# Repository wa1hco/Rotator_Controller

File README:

Rotator_Controller derives from the K3NG rotator controller code.

The changes include
--- Developed for Teensy 3 and 4 series microcontroller
--- Version for HCO_board with relays and 7 segment
--- BigFont for 4x20 lcd to make it more like the GreenHeron controller
--- Lots of changes to better suit my programming style
--- Scratchy pot filter for rotors with grounded wiper

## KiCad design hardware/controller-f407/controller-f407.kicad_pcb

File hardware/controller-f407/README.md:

# F407 controller schematic

This is the new controller, started from the outside in. The rotor interface and the AC motor drive are on `rotor_drive`. The Drive MCU and the analog front end are the next two sheets.

The directory is `hardware/controller-f407/` because ADR 0014 names the STM32F407, and the tree sits beside the imported V4 project at `hardware/controller/` without mixing files. Leave `hardware/controller/` untouched. It is the reference for the V4 TVS, snubber, and connector practice.

| File | What it is |
| --- | --- |
| `controller-f407.kicad_sch` | Root sheet. `rotor_drive`, `drive_mcu`, and `analog_input` hang off it. `+5V` and `AC_FUSED` stay no-connects until the power sheet exists. |
| `rotor_drive.kicad_sch` | Azimuth rotor connector, motor caps, triac drive, ARM relay, 26 VAC tap. |
| `drive_mcu.kicad_sch` | Drive MCU, STM32G431RBT6. Power, SWD, and the UART to the Station. |
| `analog_input.kicad_sch` | Pot front end, the VIN_RECT warning, and the ADC reference filter. |
| `rotor-drive.pdf` | Plot of both sheets, for review away from KiCad. |
| `DESIGN-NOTES.md` | What each block does, the calculations, the bill of materials, and the open questions. |
| `symbols/controller-f407.kicad_sym` | Unused TPS3823-33 symbol (the supervisor is not on the rotor sheet) and the no-pad Powerpole gland marker. |
| `footprints/controller-f407.pretty/` | The two motor-cap footprints copied from the Hammond outline, and the gland marker. |

KiCad 9. Nets leave `rotor_drive` on hierarchical labels (`AZ_CW_EN`, `AZ_CCW_EN`, `AZ_BRAKE_EN`, `ARM_EN`, `ZC_SENSE`, and the rest listed in the design notes). The pin assignment is in [the Drive note](../../docs/design/drive-controller.md). Through-hole parts are bought from Mouser. SMT parts that have a checked LCSC number say so on the symbol; the rest are TBD.

Elevation is a later copy of this sheet (ADR 0008), not a second channel here.

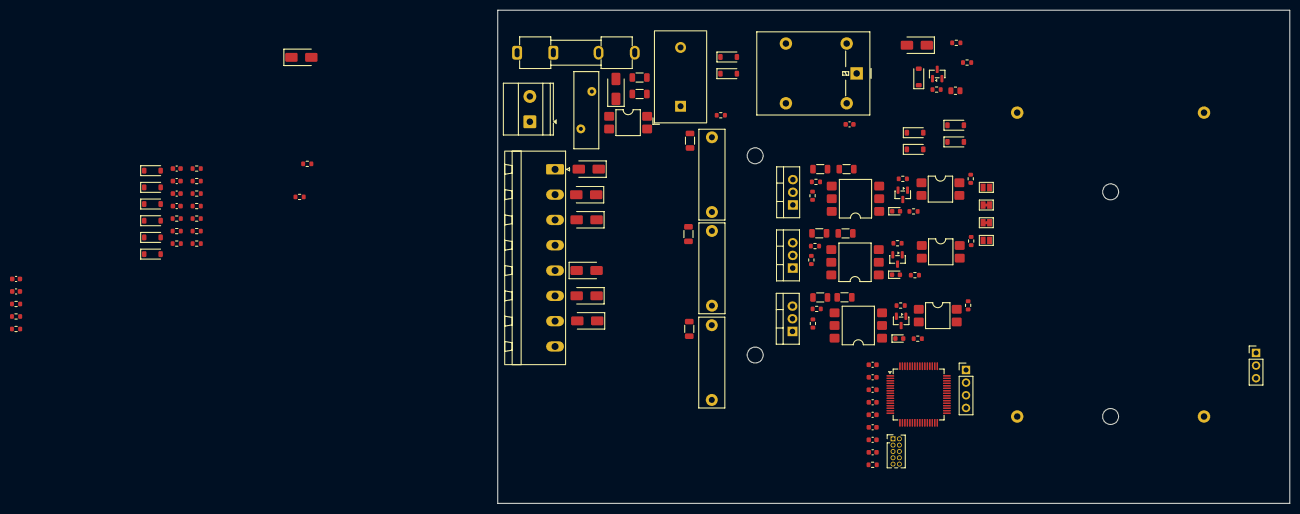
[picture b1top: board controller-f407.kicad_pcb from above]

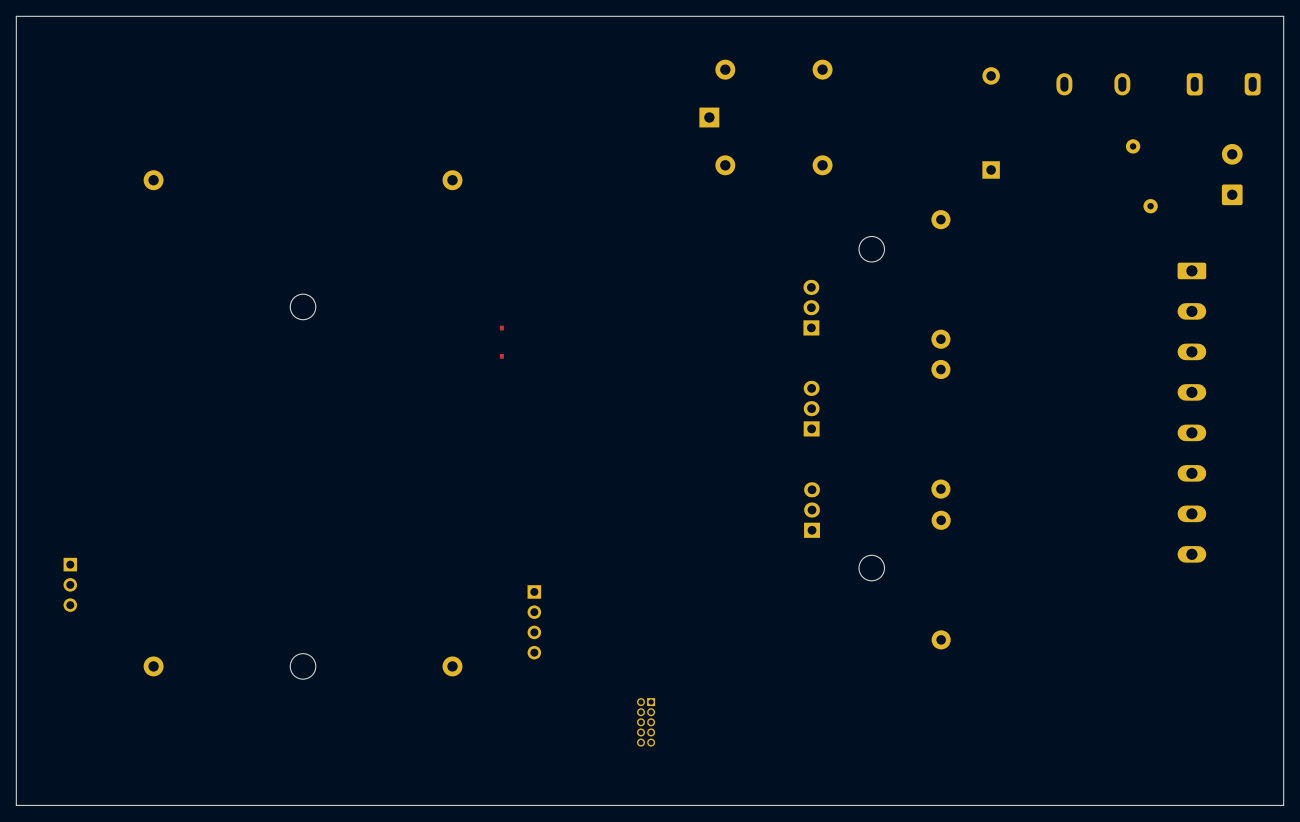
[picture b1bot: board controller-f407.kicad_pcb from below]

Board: 2 copper layers, 159.0 x 99.0 mm, 122 parts (2 on the bottom side), 72 nets, no tracks yet.

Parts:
C1, C2, C3: 100nF; C_0603_1608Metric
C4, C5, C8: 100nF; C_Rect_L18.0mm_W5.0mm_P15.00mm_FKS3_FKP3
C6: 100uF; C_Rect_KEMET_R60_P37.5_L41.5_W20_H40_Flat
C7: 33uF; C_Rect_TDK_B32526T_P37.5_L41.5_W24_H15_Upright
C9, C11, C12, C13, C14, C16, C17, C18, C19, C20: 100n; C_0603_1608Metric
C10: 1u; C_0603_1608Metric
C15: 4.7u; C_0603_1608Metric
D1, D2, D14, D15, D16, D17, D18, D20, D21, D23, D24, D25: BAT54; D_SOD-123
D3: S1M; D_SMA
D4, D8, D9, D10, D11, D12, D19, D22: SMAJ90CA; D_SMA
D5: 1N4148W; D_SOD-123
D6, D7, D13: RED; LED_0603_1608Metric
F1: T6.3A; Fuseholder_Clip-5x20mm_Keystone_3512_Inline_P23.62x7.27mm_D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
HS1: AL_BAR_10x50 + 2x NPTH 3.2; AL_BAR_10x50
J1: AC_PIGTAIL; TerminalBlock_Phoenix_MKDS-1,5-2-5.08_1x02_P5.08mm_Horizont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
J2: CDE_1to8; PhoenixContact_MSTBA_2,5_8-G-5,08_1x08_P5.08mm_Horizontal
J3: SWD; PinHeader_2x05_P1.27mm_Vertical
J4: UART; PinHeader_1x04_P2.54mm_Vertical
J5: EL_POT; PinHeader_1x03_P2.54mm_Vertical
K1: G5LE-1A4-DC5; Relay_SPDT_Omron-G5LE-1
MK1: PWR_GLAND; Panel_Gland_M16
Q1: AO3400A; SOT-23
Q2, Q4, Q6: BTA16-600SWRG; TO-220-3_Vertical
Q3, Q5, Q7: 2N7002; SOT-23
R1, R4, R5, R15, R22, R29, R33, R36, R39, R42: 10k; R_0603_1608Metric
R2, R11, R18, R25, R32, R35, R38, R41, R44: 1k; R_0603_1608Metric
R2G1, R3G1, R4G1, R8: 100k; R_0603_1608Metric
R3: 100; R_0805_2012Metric
R6, R7, R12, R14, R19, R21, R26, R28: 7.5k; R_1206_3216Metric
R9, R16, R23: 100; R_0603_1608Metric
R10, R17, R24: 180; R_0603_1608Metric
R13, R20, R27: 68; R_1206_3216Metric
R30: 10; R_0603_1608Metric
R31, R34, R37, R40: 330; R_0603_1608Metric
R43: 39k; R_0603_1608Metric
RV1: 35VAC; RV_Disc_D15.5mm_W5mm_P7.5mm
SJ1: YAE_CAP_A; SolderJumper-2_P1.3mm_Open_Pad1.0x1.5mm
SJ2: CDE_CAP_A; SolderJumper-2_P1.3mm_Bridged_Pad1.0x1.5mm
SJ3: CDE_CAP_B; SolderJumper-2_P1.3mm_Bridged_Pad1.0x1.5mm
SJ4: YAE_CAP_B; SolderJumper-2_P1.3mm_Open_Pad1.0x1.5mm
TR1: ZMCT103C; Transformer_Zeming_ZMCT103C
U1, U3, U5, U7: LTV-814S-TA1; SMDIP-4_W7.62mm
U2, U4, U6: MOC3023SM; SMDIP-6_W9.53mm
U8: STM32G431RBTx; LQFP-64_10x10mm_P0.5mm

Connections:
/+3V3: C3.1, C11.1, C12.1, C13.1, C14.1, C15.1, D1.1 (K), D14.1 (K), D16.1 (K), D18.1 (K), D21.1 (K), D24.1 (K), J3.1, J4.2, R1.1, R5.1, R15.1, R22.1, R29.1, R30.2, R31.1, R34.1, R37.1, R40.1, U8.1 (VBAT), U8.16 (VDD), U8.32 (VDD), U8.48 (VDD), U8.64 (VDD)
/ARM_EN: Q1.1 (G), R8.1, U8.55 (PD2)
/AZ_A_ADC: C17.1, R33.2, U8.8 (PC0)
/AZ_BRAKE_EN: Q3.1 (G), R4G1.1, U8.54 (PC12)
/AZ_BRAKE_SNS: R15.2, U3.4, U8.4 (PC15)
/AZ_B_ADC: C18.1, R36.2, U8.9 (PC1)
/AZ_CCW_EN: Q7.1 (G), R3G1.1, U8.39 (PC7)
/AZ_CCW_SNS: R29.2, U7.4, U8.3 (PC14)
/AZ_CW_EN: Q5.1 (G), R2G1.1, U8.38 (PC6)
/AZ_CW_SNS: R22.2, U5.4, U8.2 (PC13)
/AZ_POT_3: D9.2 (A2), J2.3, R31.2, R32.1
/AZ_POT_7: D12.2 (A2), J2.7, R34.2, R35.1
/EL_A_ADC: C19.1, R39.2, U8.10 (PC2)
/EL_B_ADC: C20.1, R42.2, U8.11 (PC3)
/I_ADC: D1.2 (A), D2.1 (K), R2.2, U8.12 (PA0)
/VIN_RECT: D3.1 (K), R43.1
/VIN_WARN: D24.2 (A), D25.1 (K), R43.2, R44.1, U8.13 (PA1)
/ZC_SENSE: R5.2, U1.4, U8.58 (PB5)
/analog_input/EL_POT_A: D19.1 (K), J5.2, R37.2, R38.1
/analog_input/EL_POT_B: D22.1 (K), J5.3, R40.2, R41.1
/rotor_drive/+5V: C2.1, D5.1 (K), K1.5, R10.1, R17.1, R24.1
/rotor_drive/AC_BUS: K1.3, Q2.2 (A2), Q4.2 (A2), Q6.2 (A2), R12.1, R13.1, R19.1, R20.1, R26.1, R27.1
/rotor_drive/AC_FUSED: D3.2 (A), D4.2 (A2), F1.2, K1.1, R7.1, RV1.1
/rotor_drive/BRK_OUT: C4.2, D8.2 (A2), J2.2, Q2.1 (A1), R11.2, U2.4, U3.2
/rotor_drive/CCW_OUT: C8.2, D11.2 (A2), J2.6, Q6.1 (A1), R25.2, SJ4.2 (B), U6.4, U7.2
/rotor_drive/CW_OUT: C5.2, D10.2 (A2), J2.5, Q4.1 (A1), R18.2, SJ1.2 (B), U4.4, U5.2
/rotor_drive/I_BIAS: C1.1, R1.2, R3.2, R4.1, TR1.1
/rotor_drive/I_CT: R2.1, R3.1, TR1.2
/rotor_drive/TB4: J2.4, SJ2.2 (B)
/rotor_drive/TB8: J2.8, SJ3.2 (B)
GNDPWR: C1.2, C2.2, C3.2, C9.2, C10.2, C11.2, C12.2, C13.2, C14.2, C15.2, C16.2, C17.2, C18.2, C19.2, C20.2, D2.2 (A), D4.1 (A1), D8.1 (A1), D9.1 (A1), D10.1 (A1), D11.1 (A1), D12.1 (A1), D15.2 (A), D17.2 (A), D19.2 (A), D20.2 (A), D22.2 (A), D23.2 (A), D25.2 (A), J1.2, J2.1, J3.3, J3.5, J3.9, J4.1, J5.1, Q1.2 (S), Q3.2 (S), Q5.2 (S), Q7.2 (S), R2G1.2, R3G1.2, R4.2, R4G1.2, R8.2, R44.2, RV1.2, U1.2, U1.3, U3.3, U5.3, U7.3, U8.15 (VSS), U8.27 (VSSA), U8.31 (VSS), U8.47 (VSS), U8.63 (VSS)
unnamed: C4.1, R13.2
unnamed: C5.1, R20.2
unnamed: C8.1, R27.2
unnamed: D5.2 (A), K1.2, Q1.3 (D)
unnamed: D6.2 (A), R10.2
unnamed: D6.1 (K), U2.1
unnamed: D7.2 (A), R17.2
unnamed: D7.1 (K), U4.1
unnamed: D13.2 (A), R24.2
unnamed: D13.1 (K), U6.1
unnamed: D14.2 (A), D15.1 (K), R32.2, R33.1
unnamed: D16.2 (A), D17.1 (K), R35.2, R36.1
unnamed: D18.2 (A), D20.1 (K), R38.2, R39.1
unnamed: D21.2 (A), D23.1 (K), R41.2, R42.1
unnamed: F1.1, J1.1
unnamed: Q2.3 (G), R9.2, R11.1
unnamed: Q3.3 (D), U2.2
unnamed: Q4.3 (G), R16.2, R18.1
unnamed: Q5.3 (D), U4.2
unnamed: Q6.3 (G), R23.2, R25.1
unnamed: Q7.3 (D), U6.2
unnamed: R6.1, R7.2
unnamed: R6.2, U1.1
unnamed: R9.1, U2.6
unnamed: R12.2, R14.1
unnamed: R14.2, U3.1
unnamed: R16.1, U4.6
unnamed: R19.2, R21.1
unnamed: R21.2, U5.1
unnamed: R23.1, U6.6
unnamed: R26.2, R28.1
unnamed: R28.2, U7.1
unnamed: C6.1, C7.1, SJ1.1 (A), SJ2.1 (A)
unnamed: C6.2, C7.2, SJ3.1 (A), SJ4.1 (A)
unnamed: J3.2, U8.49 (PA13)
unnamed: J3.4, U8.50 (PA14)
unnamed: J3.6, U8.56 (PB3)
unnamed: J4.3, U8.30 (PB10)
unnamed: J4.4, U8.33 (PB11)
unnamed: C16.1, J3.10, U8.7 (PG10)
unnamed: C9.1, C10.1, R30.1, U8.28 (VREF+), U8.29 (VDDA)

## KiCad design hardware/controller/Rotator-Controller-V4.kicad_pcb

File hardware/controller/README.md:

# V4 controller board

KiCad 9 project for the shack-side antenna rotator controller. The files
in this directory are the imported CPC1966 design: STM32F405RGT6 in
LQFP-64, ADuM4160 isolated USB, and three CPC1966 AC solid-state relays
(CW, CCW, brake).

That MCU is not the build target. The accepted part is an STM32F407VGT6
(LQFP-100, LCSC C12345) with a LAN8720A RMII PHY, and Ethernet is
standard. See `docs/decisions/0014-stm32f407-lan8720.md` and
`docs/design/mcu-ethernet-lcsc.md`. The schematic and PCB are
intentionally not edited for that change. The MCU area was barely
routed, so the next layout pass replaces the 64-pin footprint.

Newer edits that exist only on the owner's laptop are **not** in this
import. Those are the discrete-triac swap (MOC3023M + BTA16-600SW and
snubbers) and the annotated design notes. They will be added later.
Until then, `docs/design/v4-discrete-triac-change.md` is the change plan,
and the schematic still shows CPC1966 parts.

## Assembly and part fields

JLCPCB assembles every SMT part, and those parts come from the LCSC
catalog. The owner hand-solders every through-hole part, and those parts
are bought from Mouser. The record is
`docs/decisions/0013-assembly-sourcing.md`.

When symbols are updated (not done in the imported project):

- An SMT part gets an `LCSC` field whose value is the LCSC C-number
  (for example `C12345` on the STM32F407VGT6).
- A through-hole part gets a `Mouser` field with the Mouser order number.
The RJ45 candidate is the Pulse J0011D01BNL; that order number is not
confirmed yet, so the field waits until it is.

## Programming and debug (not in the schematic yet)

The next layout adds these. Details and the reasons are in
`docs/decisions/0015-configuration-and-ui.md` and the programming
addendum of `docs/design/hardware-requirements.md`. Do not put them on
the front plate.

| Function | Part | Source field |
|---|---|---|
| BOOT0 tactile, pull-down to ground, button to 3.3 V | SMT tactile. C-number TBD | `LCSC` when known |
| RESET tactile, to NRST | SMT tactile. C-number TBD | `LCSC` when known |
| PB2 (BOOT1) pull-down | SMT resistor. C-number TBD | `LCSC` when known |
| MCU HSE | 8 MHz crystal and load caps. C-numbers TBD. Not the PHY's 25 MHz C9006 | `LCSC` when known |
| USB-C CC1 and CC2 | 5.1 kΩ each to ground. C-number TBD | `LCSC` when known |
| Debug | Tag-Connect TC2050-IDC-NL pads (SWDIO, SWCLK, SWO, NRST). No part | none |
| Boot LED | SMT LED and resistor. C-numbers TBD | `LCSC` when known |

USB-C D+ does not get its own 1.5 kΩ. The ADuM4160's PIN pin is tied to
VDD2 so the isolator's upstream pull-up is present for ROM DFU and for
the application. SPU and SPD are tied high (full speed). The drawing
still straps them low.

## Source

Imported from [wa1hco/Rotator-Controller-V2](https://github.com/wa1hco/Rotator-Controller-V2),
branch `Rotator_Controller_V4`, commit
`27affb32f34605df6d436127cd1c47bb30fbcdb9`
("Removed some deleted files", 2025-10-09).

History was kept with `git filter-repo`: only the KiCad project and the
project-local libraries this board references were retained, then moved
under `hardware/controller/`. Commit hashes in this repository differ
from the source repo because the history was rewritten. The last source
commit that changed the schematic is
`b3b3aa526a4143c245adb577c08cf79c1521e6af`. Blob hashes of every imported
file match the source tip above. The source tip commit itself only
deleted files that were not imported, so it does not appear in this history.

That source tree was published under CC0-1.0. The same author licenses
the hardware in **this** repository under CERN-OHL-S-2.0
(`hardware/LICENSE`).

## What was kept

| Path | Why |
|---|---|
| `Rotator-Controller-V4.kicad_{pro,sch,pcb}` | The board |
| `RotatorController.kicad_sym`, `RotatorController.pretty/` | CPC1966 symbol and footprint, both used |
| `LightPipe.kicad_sym`, `Lightpipe.pretty/` | LP4-EP light pipe, used |
| `NKK_BB15AH.pretty/` | Front-panel switch footprint, used |
| `sym-lib-table`, `fp-lib-table` | Project library tables |
| `.gitignore` | KiCad backup and cache rules from the source project |

Library nicknames and `${KIPRJMOD}` URIs are unchanged for the libraries
that remain, so opening the project from this directory does not depend
on a global KiCad library path. After the move, table entries for
libraries that were **not** imported (Teensy, Button, Pushbutton) were
removed. Leaving them would make KiCad look for missing directories.

Symbols are also embedded in the schematic, and footprints are embedded
in the PCB, which is how KiCad 6+ projects open when a library is absent.
The project-local libraries are still here so "Update from library" and
a standalone open both work.

Standard-part 3D models are **not** vendored. The board references
`${KICAD8_3DMODEL_DIR}` and `${KICAD9_3DMODEL_DIR}` from the KiCad
installation. There is no project-local 3D model for the STM32 board.
The only STEP files in the source branch belonged to the unused Teensy
library.

## What was left in the source repo

- `Software/` — the previous firmware tree. This repository's firmware is
  a new core under `software/firmware/`.
- `Datasheets/` — manufacturer PDFs (about 42 MB). Not redistributed here.
- `Teensy.pretty/`, `Teensy.kicad_sym`, `teensy.kicad_sym` — not referenced
  by the V4 STM32 schematic or PCB. Third-party MIT-licensed footprints.
- `Button.pretty/`, `2024-07-13_20-59-04.kicad_sym`, and the stray
  `Button_Switch_THT:Omron.pretty/` — not used by the V4 board.
- `Rotator-Controller-V4.kicad_sch_old` — schematic backup.
- `jlcpcb/project.db` — plugin database.
- `Rotor Enclosures.odt`, `Rotor and Controller Schematics.docx`,
  `Rotator-Controller-V4.ods` — older office notes. Current design writing
  is in `docs/design/`.
- KiCad backups, lock files, `fp-info-cache`, and autosaves were not in
  git and are ignored.

## Open

KiCad 9 or newer:

```bash
kicad hardware/controller/Rotator-Controller-V4.kicad_pro
```

The schematic has many known ERC violations (unconnected MCU pins and
similar). CI runs ERC and DRC to produce reports and does not fail the
build on those violations. See the root README.

The Hammond 1455N1601 board outline and the end-plate drawings are in
[`mechanical/`](mechanical/README.md). That KiCad project is not the V4
board. Leave `Rotator-Controller-V4.kicad_*` alone when opening it.

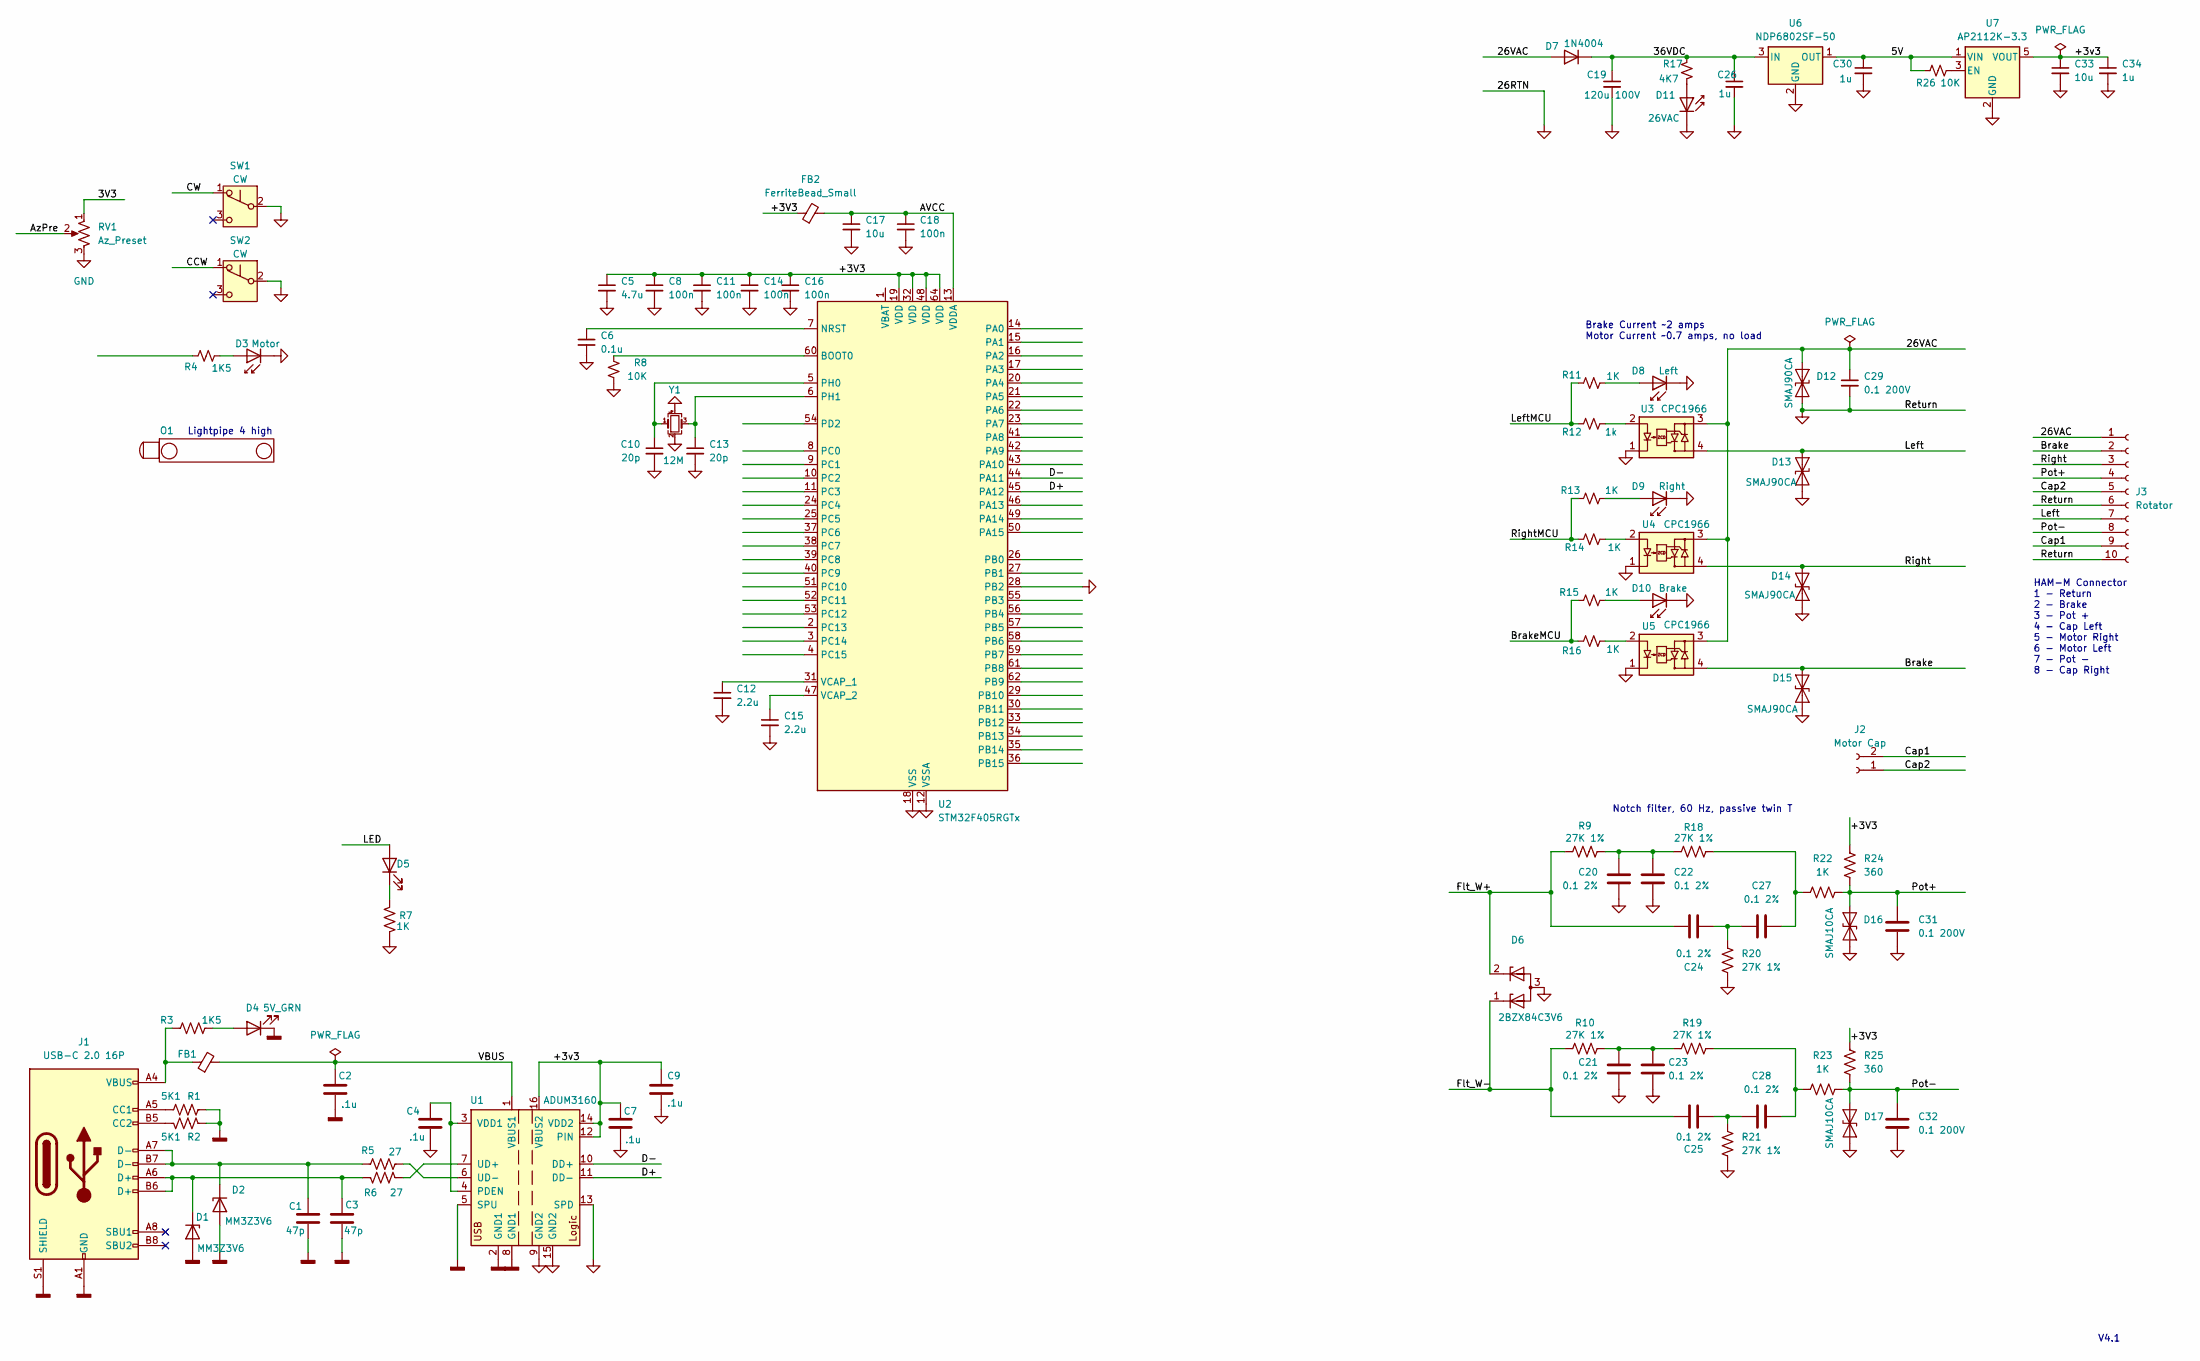
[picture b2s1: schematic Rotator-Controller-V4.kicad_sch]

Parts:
C1, C3: 47p; C_0603_1608Metric; LCSC C1671
C2, C4, C7, C9: .1u; C_0603_1608Metric; LCSC C14663
C5: 4.7u; C_0603_1608Metric
C6: 0.1u; C_0603_1608Metric
C8, C11, C14, C16, C18: 100n; C_0603_1608Metric
C10, C13: 20p; C_0603_1608Metric
C12, C15: 2.2u; C_0603_1608Metric
C17, C33: 10u; C_0603_1608Metric
C19: 120u 100V; CP_Elec_8x10
C20: 0.1 2%; C_1206_3216Metric_Pad1.33x1.80mm_HandSolder; LCSC C6478705
C21, C22, C23, C24, C25, C27, C28: 0.1 2%; C_1206_3216Metric_Pad1.33x1.80mm_HandSolder
C26, C30: 1u; C_1206_3216Metric_Pad1.33x1.80mm_HandSolder
C29, C31, C32: 0.1 200V; C_1206_3216Metric_Pad1.33x1.80mm_HandSolder
C34: 1u; C_0603_1608Metric
D1, D2: MM3Z3V6; D_SOD-323; LCSC C116949
D3: Motor; LED_0402_1005Metric
D4: 5V_GRN; LED_0402_1005Metric; LCSC C965804
D5: White; LED_0402_1005Metric; LCSC C965804
D6: 2BZX84C3V6; SOT-23
D7: 1N4004; D_SOD-123F
D8: Left; LED_0402_1005Metric
D9: Right; LED_0402_1005Metric
D10: Brake; LED_0402_1005Metric
D11: 26VAC; LED_0402_1005Metric
D12, D13, D14, D15: SMAJ90CA; D_SMA
D16, D17: SMAJ10CA; D_SMA
FB1: FerriteBead_Small; L_0805_2012Metric; LCSC C1017
FB2: FerriteBead_Small; L_0805_2012Metric
J1: USB-C 2.0 16P; USB_C_Receptacle_G-Switch_GT-USB-7010ASV; LCSC C2988369
J2: Motor Cap; PinHeader_1x02_P2.54mm_Vertical
J3: Rotator; TE_MATE-N-LOK_1-770971-x_2x05_P4.14mm_Horizontal
O1: LP4-EP
R1, R2: 5K1; R_0603_1608Metric; LCSC C23186
R3: 1K5; R_0603_1608Metric; LCSC C21190
R4: 1K5; R_0603_1608Metric
R5, R6: 27; R_0402_1005Metric; LCSC PN C25190
R7: 1K; R_0603_1608Metric; LCSC C21190
R8, R26: 10K; R_0603_1608Metric
R9, R10, R18, R19, R20, R21: 27K 1%; R_0603_1608Metric
R11, R13, R14, R15, R16, R22, R23: 1K; R_0603_1608Metric
R12: 1k; R_0603_1608Metric
R17: 4K7; R_0603_1608Metric
R24, R25: 360; R_0603_1608Metric
RV1: Az_Preset; Potentiometer_Alps_RK09K_Single_Horizontal
SW1, SW2: CW; SW_NKK_BB15AH
U1: ADUM3160; SOIC-16W_7.5x10.3mm_P1.27mm
U2: STM32F405RGTx; LQFP-64_10x10mm_P0.5mm
U3, U4, U5: CPC1966
U6: NDP6802SF-50; SOT-89-3
U7: AP2112K-3.3; SOT-23-5
Y1: 12M; Crystal_SMD_2016-4Pin_2.0x1.6mm

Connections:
/3V3: RV1.1
/5V: C30.1, R26.1, U6.1 (OUT), U7.1 (VIN)
/26VAC: C29.1, D7.2 (A), D12.2 (A2), J3.1, U3.3, U4.3, U5.3
/36VDC: C19.1, C26.1, D7.1 (K), R17.2, U6.3 (IN)
/+3V3: C5.1, C8.1, C11.1, C14.1, C16.1, FB2.1, R24.1, R25.1, U2.19 (VDD), U2.32 (VDD), U2.48 (VDD), U2.64 (VDD)
/+3v3: C7.1, C9.1, C33.1, C34.1, U1.12 (PIN), U1.14 (VDD2), U1.16 (VBUS2), U7.5 (VOUT)
/AVCC: C17.1, C18.1, FB2.2, U2.13 (VDDA)
/AzPre: RV1.2
/Brake: D15.2 (A2), J3.2, U5.4
/BrakeMCU: R15.1, R16.1
/CCW: SW2.1 (A)
/CW: SW1.1 (A)
/Cap1: J2.2, J3.9
/Cap2: J2.1, J3.5
/D+: U1.11 (DD-), U2.45 (PA12)
/D-: U1.10 (DD+), U2.44 (PA11)
/Flt_W+: C24.1, D6.2 (K), R9.1
/Flt_W-: C25.1, D6.1 (K), R10.1
/LED: D5.2 (A)
/Left: D13.2 (A2), J3.7, U3.4
/LeftMCU: R11.1, R12.1
/Pot+: C31.2, D16.2 (A2), J3.4, R22.2, R24.2
/Pot-: C32.2, D17.2 (A2), J3.8, R23.2, R25.2
/Right: D14.2 (A2), J3.3, U4.4
/RightMCU: R13.1, R14.1
/VBUS: C2.1, FB1.2, U1.1 (VBUS1)
GND: C4.2, C5.2, C6.2, C7.2, C8.2, C9.2, C10.2, C11.2, C12.2, C13.2, C14.2, C15.2, C16.2, C17.2, C18.2, C19.2, C20.2, C21.2, C22.2, C23.2, C26.2, C29.2, C30.2, C31.1, C32.1, C33.2, C34.2, D3.1 (K), D6.3 (A), D8.1 (K), D9.1 (K), D10.1 (K), D11.1 (K), D12.1 (A1), D13.1 (A1), D14.1 (A1), D15.1 (A1), D16.1 (A1), D17.1 (A1), J3.6, J3.10, R7.2, R8.1, R20.2, R21.2, RV1.3, SW1.2 (B), SW2.2 (B), U1.9 (GND2), U1.13 (SPD), U1.15 (GND2), U2.12 (VSSA), U2.18 (VSS), U2.28 (PB2), U2.63 (VSS), U3.1, U4.1, U5.1, U6.2 (GND), U7.2 (GND), Y1.2, Y1.4
GNDD: C1.2, C2.2, C3.2, D1.2 (A), D2.2 (A), D4.1 (K), J1.A1 (GND), J1.A12 (GND), J1.B1 (GND), J1.B12 (GND), J1.S1 (SHIELD), R1.1, R2.1, U1.2 (GND1), U1.5 (SPU), U1.8 (GND1)
unnamed: C20.1, C22.1, R9.2, R18.1
unnamed: C21.1, C23.1, R10.2, R19.1
unnamed: C24.2, C27.1, R20.1
unnamed: C25.2, C28.1, R21.1
unnamed: C27.2, R18.2, R22.1
unnamed: C28.2, R19.2, R23.1
unnamed: C3.1, D1.1 (K), J1.A6 (D+), J1.B6 (D+), R6.2
unnamed: C1.1, D2.1 (K), J1.A7 (D-), J1.B7 (D-), R5.2
unnamed: D3.2 (A), R4.2
unnamed: D4.2 (A), R3.2
unnamed: D5.1 (K), R7.1
unnamed: D8.2 (A), R11.2
unnamed: D9.2 (A), R13.2
unnamed: D10.2 (A), R15.2
unnamed: D11.2 (A), R17.1
unnamed: FB1.1, J1.A4 (VBUS), J1.A9 (VBUS), J1.B4 (VBUS), J1.B9 (VBUS), R3.1
unnamed: J1.A5 (CC1), R1.2
unnamed: J1.B5 (CC2), R2.2
unnamed: R12.2, U3.2
unnamed: R14.2, U4.2
unnamed: R16.2, U5.2
unnamed: C4.1, U1.3 (VDD1), U1.4 (PDEN)
unnamed: R6.1, U1.7 (UD+)
unnamed: R5.1, U1.6 (UD-)
unnamed: R8.2, U2.60 (BOOT0)
unnamed: C6.1, U2.7 (NRST)
unnamed: C10.1, U2.5 (PH0), Y1.1
unnamed: C13.1, U2.6 (PH1), Y1.3
unnamed: C12.1, U2.31 (VCAP_1)
unnamed: C15.1, U2.47 (VCAP_2)
unnamed: R26.2, U7.3 (EN)

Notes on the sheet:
HAM-M Connector 1 - Return 2 - Brake 3 - Pot + 4 - Cap Left 5 - Motor Right 6 - Motor Left 7 - Pot - 8 - Cap Right
V4.1
Brake Current ~2 amps Motor Current ~0.7 amps, no load
Lightpipe 4 high
Notch filter, 60 Hz, passive twin T

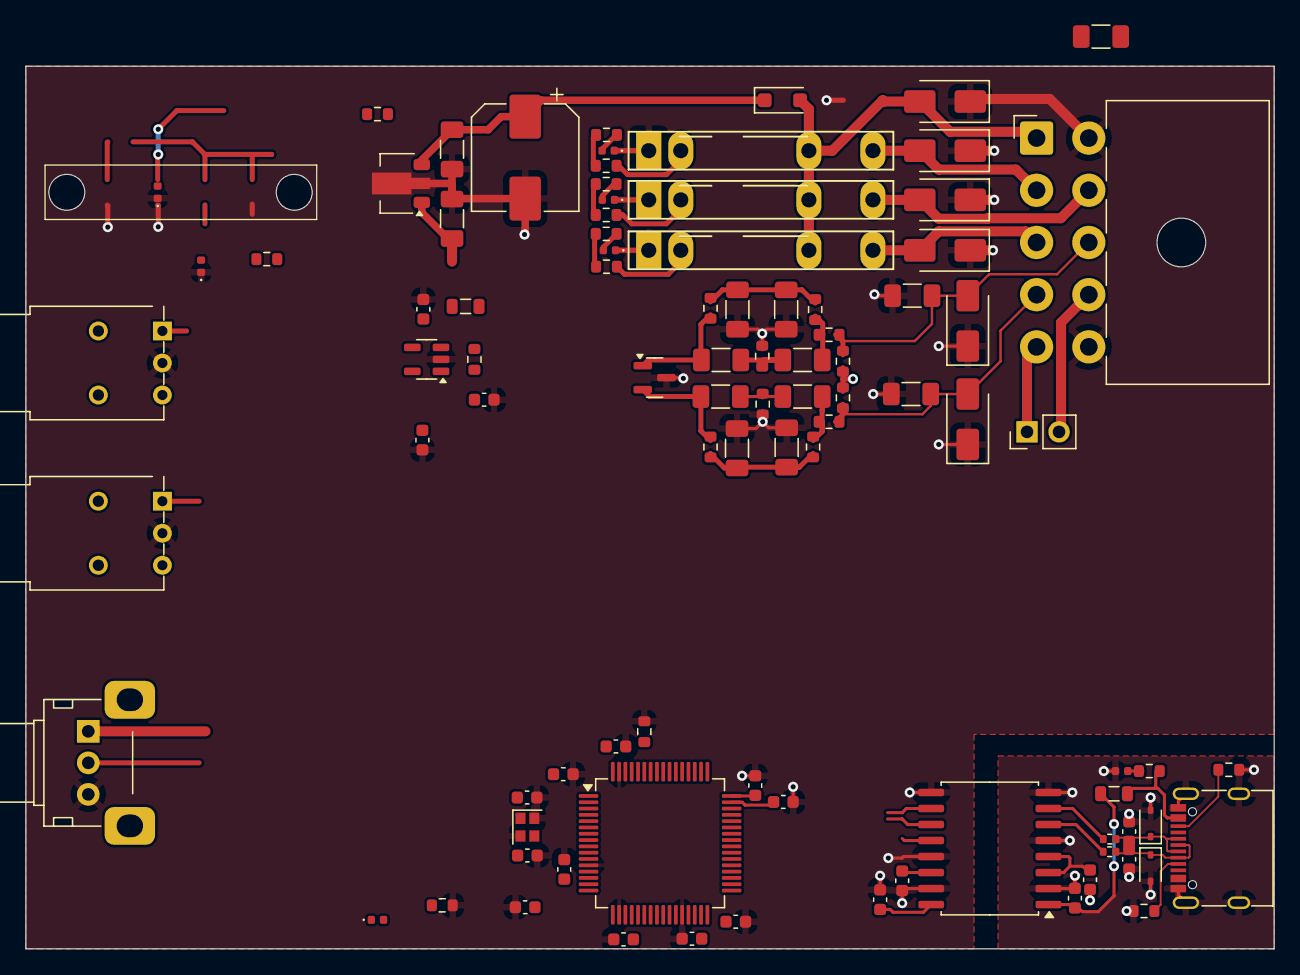
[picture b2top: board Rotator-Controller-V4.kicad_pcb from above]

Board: 2 copper layers, 99.0 x 70.0 mm, 94 parts (0 on the bottom side), 54 nets.

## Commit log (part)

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2017-01-21 First commit of new project - K3NG rotator controller software with a bunch of changes to fit my style - developing on Teensy with Teensyduino libraries and Arduino IDE - Clone of GreenHerron control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
2017-01-21 blank .gitignore for now
2017-01-21 forgot to add README
2017-01-22 Added creative commons license
2017-01-22 was editing in the wrong folder, overwrite the files Changed to wa1hco on initial screen Enable debug, but gotta connect a serial port Made the Teensy pins table look better
2017-01-22 white space wa1hco is the author
2017-01-22 Renamed some files to remove mention of GreenHerron Started on making a new BigFont display driver without elevation
2017-01-23 modified display function is in a separate folder Doh! don't include file, just let linker find it
2017-01-24 Pulled update_big_display() back into mainline.
2017-01-24 stripped out option to configure some of the LCDs misc white space changes while scanning code
2017-01-29 BigFonts.h improved comments Print leading zeros in Az GreenHerronFonts.h deleted file Rotator-Controller.ino lots of white space changes for my style Speed up display update move locations on LCD to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
2017-01-30 display_update() in several pieces Got rid if row 0 and 1 stuff
2017-02-04 documentation, white space cleanups Start to make az_preset work with realtime display of setting
2017-02-04 renamed rotator controller back to without the "E". changed due to eclipse testing
2017-02-04 reverted < > to " " after playing with eclipse
2017-02-12 Copy in revised files from recent changes under Eclipse.
2017-02-12 rename .ino with underscore
2017-02-12 Pulled out the setting, macros, and dependencies into seperate include files
2017-02-12 removed BitFonts.h file, rearranged
2017-02-12 pulled dependencies, macros, and settings into separate files. This commit adds them
2017-02-12 changed name of .ino file
2017-02-12 combined several display functions into one display.cpp, defined in display .h
2017-02-12 Adding the display .cpp and .h files.
2017-02-12 Remove three function files that got merged into display.cpp
2017-02-13 intermediate state, problems with refactoring global variables
2017-02-18 Reversed course...was trying to make subroutines for the display
2017-02-19 Pulled all display functions into a separate file, resolved all externs, created function prototypes, etc
2017-02-19 small edits
2017-02-19 display functions in separate file
2017-02-19 display in functions
2017-02-21 Completed refactoring to move all display functions into Display.cpp, including globals into private variables.
2017-05-29 Cleanups in prep for converting to H-Bridge controller for DC rotator
2017-05-29 Working with H-Bridge and accel/decel. Stops about 3 degrees short and leaves the PWM running for some seconds. Then it times out and stops
2017-06-05 Minor cleanups in code style
2022-03-11 Change to use VS Code
2022-03-18 separate long file into global, serial, etc
2022-03-18 stage all and commit
2022-03-18 fixed global variables started playing with reading ADC with grounded wiper
2022-03-18 command line commit to remove files
2022-04-09 Converted ADC reading to interrupts at 500 Hz added 'hco' to startup on the LCD display Implement reading buttons from HCO board Converted hardware rotator pot from 5V pullup to 3.3V for better regul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
2022-04-28 Converted to MAX7721 display driver
2022-04-30 removedd MAX6959 code
2022-05-04 Set ADC pins to input mode to prevent jump in reading near midscale Calculate pot resistor from end to wiper, supposed to total 500 Ohms Dirty wiper causes sum to rise, offering option for calibratio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
2022-05-07 Playing with ways to cancel effect of wiper resistance
2022-05-18 Add Bob wa8usa equation to remove wiper glitches
2022-05-28 Removed all MAX6959 code
2022-05-28 Updated .gitignore
2022-05-28 Moved includes and src into corresponding folders, removed unused files
2022-05-29 revised HCO_board button handling press and hold 2nd button to calibrate removed function call prototypes not used pulled apart the large Rotator_Controller.cpp into seperate files removed unnecessar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
2022-06-04 analog_az is sensor reading calibration is working Rotate to az working after AzFiltered = azimuth; turned off debugging switches
2022-06-04 Fixed another case when needed analog_az rather than azimuth
2022-06-04 Calibration button presses Display.cpp, move SPI transfer around analog_az replaces azimuth in calibration
2022-06-04 wrote to eeprom conditional on DEBUG_EEPROM
2022-06-05 Fix some problems with calibration add \C command to display Voltages and cal info
2022-06-09 fixed display of low order digit
2024-05-07 Broke out Setup.cpp to make it easier to find.
2024-05-07 Remove reference to unused function
2024-05-07 Broke out the Read Azimuth ISR to make it easier to find
2024-05-07 json changes
2024-05-07 Add ignore lines for VS Code
2024-05-07 merged changes related to vs code .gitignore
2024-05-07 remove .gitignore.ori merge artifact
2024-05-07 clarify README
2024-05-07 after manually merging hco_board_2 into master
2024-05-07 bunch of vs code and platform io changes after manual merge
2024-05-07 restore .pio removed by mistake
2024-05-08 manual merge of board 2 branch into master
2024-05-08 manual merge .gitignore from board 2
2024-05-08 manual merge
2024-05-08 json changes, probably should gitignore most or all
2024-05-08 probably should gitignore most of these
2024-05-08 why is .elf not gitignore'd?
2024-05-08 removed eclipse related line
2024-05-08 test .gitignore changes
2024-05-09 git remove so gitignore works
2024-05-09 restore *.elf pattern to gitignore
2024-05-09 gitignore .pio folder tree
2024-06-20 Added files Update board outline based on measurements Moved connectors to new board outline
2024-06-21 Moved Teensy into position, adjusted related traces
2024-06-26 Mid layout of smaller pcb with separately mounted cap still need to assign cap connector Added 4 high light pipe and 0805 LEDs, need to create footprint
2024-06-27 Simplified symbol and footprint for Teensy4.0 to remove unused pins Corrected error where footprints reverted to through-hole (mystery)
2024-07-02 Modifications to suppot CDE rotators Split display code for LCD vs MAX7221 7 segment Polishing global variables Adding code for azimuth preset pot, work in progress
2024-07-03 Completed Azimuth Preset pot function Refactored preset pot reading code for cleaner implementation, IMNSHO
2024-07-09 Removed .pio from cache to make .gitignore work
2024-07-09 removed .vscode/* from cache to make .gitignore work
2024-07-09 Moved some #ifdef into dependencies.h, make things more orderly
2024-07-09 cleaning up for .gitignoreO
2024-07-09 more cleanup for .gitignore
2024-07-09 Remove two json files, again?
2024-07-09 Removed some apparently unneeded include files
2024-07-10 moved several header files into dependencies.h include dependencies.h almost everywhere improved comments related to solving for azimuth pot wiper voltage
2024-07-10 minor edits
2024-07-10 Add headers to files move functions into initialize_function.cpp
2024-07-13 Brought in Octave ReadSerial script to plot azimuth algorithm global_variables Modified ADC and azimuth calculation data global_variables Moved some variables from global to local Clarified naming of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
2024-07-14 Homing in on final release add ground to pot and button mounting pads added start of dimensions and front panel sketch
2024-07-18 rewrote calibration from HCO button committed simplified include files, some more
2024-07-19 Absorbed eeprom_local.h into dependencies.h
2024-07-26 Simplify headers Simplify a few debug options
2024-08-29 Created V3 branch for new board with 3.6V zeners for protection
2024-08-29 Adapting to V3 wiring to switches and teensy
2024-08-30 Working towards branches for each hardware version Cleaned up dependencies Cleaned up definition of Teensy pins Changed whitespace in StateMachine to make it more compact and easier to decode
2024-08-30 extracted cheat sheet for serial commands removed Service_Blink_LED.h, not needed made some temporary debug changes to rotator_features.h made Display_MAX7221 more robust to configuration options Inp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
2024-08-30 turned off debug
2024-08-30 SerialCommands.txt, extracted from serial commands function dependencis.h, fix some dependency inter locks global_variables.h, can't include ifdefs from dependencies.h rotator_features.h change relat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
2024-08-30 changed date
2024-08-31 removed date, it belongs in dependencies.h
2024-08-31 Same changes as V2
2025-06-12 trying to remember how this all works...
2025-09-28 Merged software from V2 Started looking at using STM32 series MCU instead of teensy
2025-09-30 More work on schematic Started software conversion to STM32F405 MCU

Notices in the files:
hardware/controller/Rotator-Controller-V4.kicad_pcb:
WA1HCO (c) 2025
